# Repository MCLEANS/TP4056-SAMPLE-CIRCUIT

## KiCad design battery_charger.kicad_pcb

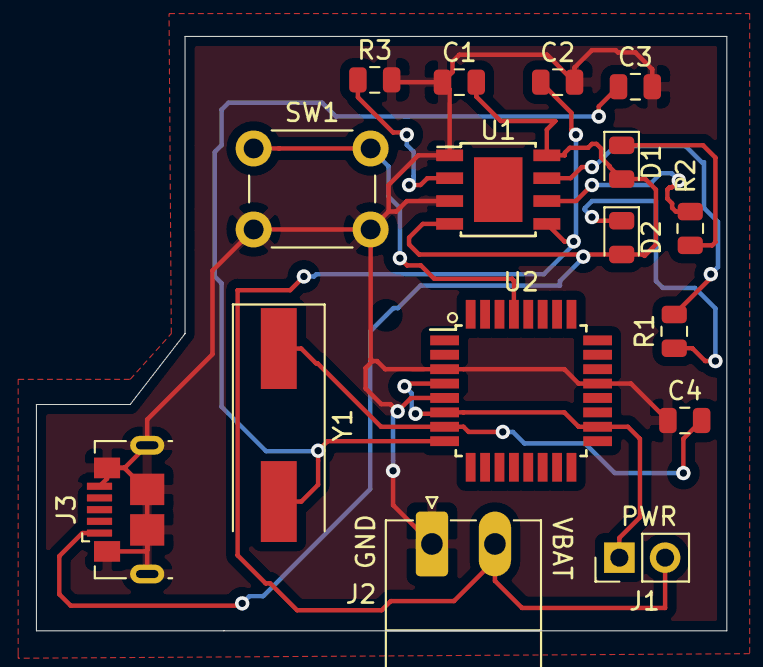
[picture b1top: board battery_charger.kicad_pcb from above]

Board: 2 copper layers, 38.4 x 33.0 mm, 16 parts (0 on the bottom side), 12 nets.

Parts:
C1, C2: 10uF; C_0805_2012Metric
C3, C4: C; C_0805_2012Metric
D1, D2: LED; LED_0805_2012Metric
J1: Conn_01x02_Male; PinHeader_1x02_P2.54mm_Vertical
J2: Conn_01x02_Male; PhoenixContact_MC_1,5_2-G-3.5_1x02_P3.50mm_Horizontal
J3: USB_B_Micro; USB_Micro-B_GCT_USB3076-30-A
R1, R2, R3: R; R_0805_2012Metric
SW1: SW_Push; SW_PUSH_6mm_H5mm
U1: TP4056; TP4056_SOP-8-PP
U2: ATmega328P-AU; TQFP-32_7x7mm_P0.8mm
Y1: Crystal; Crystal_SMD_HC49-SD

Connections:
GND: C1.1, C2.2, C3.2, C4.1, J2.1, J3.5, J3.6, R3.2, SW1.2, U1.1, U1.3, U2.3, U2.5, U2.21
unnamed: C3.1, U2.8, Y1.2
unnamed: C4.2, U2.7, Y1.1
unnamed: D1.1, R2.1
unnamed: D2.1, R1.1
unnamed: R1.2, U1.7
unnamed: R2.2, U1.6
unnamed: R3.1, U1.2
unnamed: SW1.1, U2.29
VBAT: C2.1, J1.2, J2.2, U1.5
VCC: J1.1, U2.4, U2.6, U2.18
Vin: C1.2, D1.2, D2.2, J3.1, U1.4, U1.8

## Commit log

2020-03-12 battery charger netlist
2020-03-12 Kicad project file'
2020-03-12 Routed circuit
2020-03-14 included dimensions
